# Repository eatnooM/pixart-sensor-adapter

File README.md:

# pixart-sensor-adapter

License: CC BY-SA 4.0

Allows interfacing with a Wiimote camera over I2C for GUN4IR.

Variants are present to allow use of the module either socketed as you'd find it on the Wiimote, or unsocketed for more compact installs.

I've only clocked a few hours actually _using_ these, so run this off at your own risk.

## Inline board

The inline board should be ordered in 0.8mm thickness, otherwise you won't be able to solder to the pads on the camera!
If ordering from OSHPark, I'd recommend the panelised version as they tend to put panel tabs on the edge connectors which can make for annoying cleanup before the boards are usable.

It's a pain to solder the camera module directly to the board, so I'd strongly recommend using the jig from RetroMidget's shell (see below) to aid with this, or running off [the standalone camera module jig](inline/printables/Wii-IR-camera-solder-guideGun4IR-v7.stl) graciously provided by Gzus348.

### Shell

If you're using the inline board, I would strongly recommend you check out [RetroMidget's camera enclosure](https://github.com/slikvik55/Lightgun3DParts/tree/main/WiiCamEnclosure). This 3D-printable enclosure is currently verified to fit the v1.0 board (but also fit the v1.2 board as long as you omit the rear cover) and enables you to install directly (such as in a GunCon 1) by simply tightening the nuts to hold it in place in the shell, or using prints such as JayBee's Gun4IR GunCon mounts ([GunCon 1](https://www.gun4ir.com/products/copy-of-gun4ir-diy-cam-and-rumble-holder-sets), [GunCon 2](https://www.gun4ir.com/products/gc1-gun4ir-diy-cam-and-rumble-holders)) to secure the camera and a fish-eye lens for use closer to your display.

I have a project to make a shell for the newer versions of this board that make use of the slimmer profile to fit in some tighter places (such as the barrel of a Blaze Scorpion 2, which is slightly too narrow for the DFRobot Gravity camera), but sit tight for news on this.

### IR Pass Filter

To prevent the camera from picking up visible-light sources as well as the infrared from your emitters, it is recommended to add an IR pass filter in front of the camera. This cuts down on camera erroneously detecting bright lights instead of your IR points.

If salvaging from whole Wii remotes including the shell, you'll already have the IR pass filter - this is the black-coloured plastic in the front of the shell. If you got hold of a job lot of bare boards, however, you will need to purchase some filter. I've been using the filter found in [this eBay listing](https://www.ebay.co.uk/itm/397673945348) - it's nice and thin, making it easier to cut down to size and fit in a build, and 100mm x 100mm will serve for a lot of builds if you're efficient at cutting them out. If this listing isn't available for you, there are similar listings [on Aliexpress](https://www.aliexpress.com/w/wholesale-infrared-pass-filter-940nm.html). The most important aspect of the filter is that it passes 940nm wavelength your emitters (presumably) use, and ideally blocks as much of everything else as possible.

To cut the filter, I'd recommend a rotary tool. If you have particularly sharp flush cutters, these can do the job if you're careful but I've had these split the plastic in inconvenient places so it's not my first choice. You can repeatedly score the plastic with a sharp knife to get a square of roughly the right size and then file into the desired shape, but this may take a while. You'll then need to attach this in front of the camera:

- The simplest way to attach the filter is to cut a circle of the filter to the same diameter as your shell, apply a little hot glue to the front of the shell you're using and stick it in place. If it's good enough for DFRobot, it's good enough for us. If you've dabbled in phone repair before, T7000/B7000 or similar glues will also do a great job. Just be sure to keep the glue away from the part directly in front of the camera.
- If you're using [RetroMidget's shell](https://github.com/slikvik55/Lightgun3DParts/tree/main/WiiCamEnclosure), there's a smaller circular window so you can save on a little material and only cover this area up with the filter. 

If using a wide angle or fish eye lens, there are some other convenient places to stick the filter:

- The wide angle lens adapters in the printables section all have a taper that's pretty forgiving to glue the filter into as long as you can cut it into a rough circle so there aren't big gaps for unfiltered light to pass through.
- There's a lip on the inside of the lens too - you can fit a thin filter in here.

## Ordering

Either download the gerbers from [the current release](https://github.com/eatnooM/pixart-sensor-adapter/releases/latest) or run off directly from OSHPark ([Inline](https://oshpark.com/shared_projects/reO6OkLE) / [Socketed](https://oshpark.com/shared_projects/FovxzPdv).
See below for the Bill of Materials - these can be purchased from your preferred electronic component distributor but I've provided LCSC and Mouser links for convenience.

## BOM

| Reference | Value | Link |
|-----------|-------|------|
| C1 | 0.1uF | [LCSC - YAGEO CC0603KRX7R9BB104](https://www.lcsc.com/product-detail/_YAGEO-_C14663.html) / [Mouser - KYOCERA 06035C104KAT4A](https://www.mouser.com/ProductDetail/KYOCERA-AVX/06035C104KAT4A?qs=wQ3bP3iXTzYfFzAFm7vUeQ%3D%3D) |
| C2, C3 | 1uF | [LCSC - YAGEO CC0603JRX7R7BB105](https://www.lcsc.com/product-detail/_YAGEO-_C519560.html) / [Mouser - KYOCERA 06035C105KAT2A](https://www.mouser.com/ProductDetail/KYOCERA-AVX/06035C105KAT2A?qs=%252BdQmOuGyFcGCdIIWh6fU7Q%3D%3D)|
| R1, R2 | 2.7KΩ | [LCSC - YAGEO RC0603FR-072K7L](https://www.lcsc.com/product-detail/_YAGEO-_C114612.html) / [Mouser - Panasonic ERJ-3GEYJ272V](https://www.mouser.com/ProductDetail/Panasonic/ERJ-3GEYJ272V?qs=sGAEpiMZZMvdGkrng054tw5%2FFYq5P%2FDo1QNxauZrLUw%3D) |
| R3 | 33KΩ | [LCSC - VISHAY CRCW060333K0FKEA](https://www.lcsc.com/product-detail/C844778.html) / [Mouser - Panasonic ERJ-3GEYJ333V](https://www.mouser.com/ProductDetail/Panasonic/ERJ-3GEYJ333V?qs=JjxTDIFmKPQB8Hd2hIsG7w%3D%3D) |
| U1 | Wiimote camera module – salvaged from official wiimote | Salvaged |
| U2 | AP2112-3.3V | [LCSC](https://www.lcsc.com/product-detail/_Diodes-Incorporated-_C51118.html) / [Mouser](https://www.mouser.com/productdetail/Diodes-Incorporated/AP2112K-3.3TRG1?qs=x6A8l6qLYDDPYHosCdzh%2FA%3D%3D) |
| X1 | 24-25MHz SMD3225 active crystal oscillator | [LCSC - YXC OT2EL4C4JI-111OLP-24M](https://www.lcsc.com/product-detail/Oscillators_YXC-OT2EL4C4JI-111OLP-24M_C5203548.html) / [Mouser - KYOCERA KC3225K24.0000C1GE00](https://www.mouser.com/ProductDetail/KYOCERA-AVX/KC3225K24.0000C1GE00?qs=rfsXwfL%252BOM9DBu9I0fBoew%3D%3D) |

When using with OpenFIRE, the following amendments can be made:
- As VCC is already 3.3V, U2, C2, and C3 can be omitted (and JP1 should be bridged to connect VCC straight to the camera)
- OpenFIRE supports generating the 24MHz clock signal from the RP2040 directly, meaning you can wire this to the CLK and omit X1 and C1.

## Credits

[JayBee](https://www.gun4ir.com/) - creator of Gun4IR - sharing the schematic

Gzus348 - creating the camera jig

[RetroMidget](https://github.com/slikvik55) - creator of the lovely shell for the inline boards

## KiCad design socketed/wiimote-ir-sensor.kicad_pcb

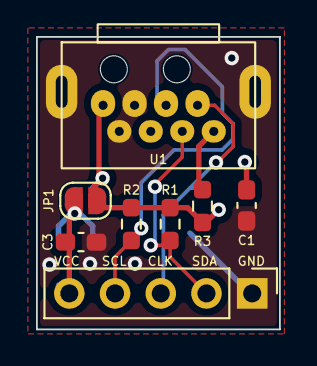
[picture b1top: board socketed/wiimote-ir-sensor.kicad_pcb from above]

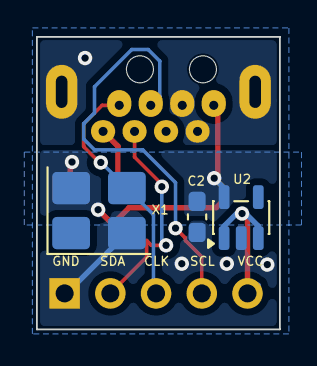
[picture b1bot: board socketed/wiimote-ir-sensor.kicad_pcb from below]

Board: 2 copper layers, 13.5 x 16.2 mm, 11 parts (3 on the bottom side), 7 nets.

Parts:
C1: 0.1uF; C_0603_1608Metric_Pad1.08x0.95mm_HandSolder
C2, C3: 1uF; C_0603_1608Metric_Pad1.08x0.95mm_HandSolder
J1: Conn_01x05_Pin; PinHeader_1x05_P2.54mm_Vertical
JP1: SolderJumper_2_Open; SolderJumper-2_P1.3mm_Open_RoundedPad1.0x1.5mm
R1, R2: 2.7K; R_0603_1608Metric_Pad0.98x0.95mm_HandSolder
R3: 33K; R_0603_1608Metric_Pad0.98x0.95mm_HandSolder
U1: wiimote-pixart-camera
U2: AP2112-3.3V; SOT-23-5
X1: SG3225CAN 24.0000M-TJGA3; Oscillator_SMD_SeikoEpson_SG8002CE-4Pin_3.2x2.5mm_HandSolde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

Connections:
+3.3V: C1.1, C2.1, JP1.2 (B), R1.1, R2.2, R3.1, U1.1 (VCC), U2.5 (VOUT), X1.4 (VCC)
/CLK: J1.3, U1.7 (CLK), X1.3 (OUT)
/SCL: J1.4, R2.1, U1.5 (SCL)
/SDA: J1.2, R1.2, U1.6 (SDA)
GND: C1.2, C2.2, C3.2, J1.1, U1.2 (GND), U1.3 (GND), U1.MP, U2.2 (GND), X1.2 (GND)
unnamed: R3.2, U1.8 (RESET)
VCC: C3.1, J1.5, JP1.1 (A), U2.1 (VIN), U2.3 (EN)

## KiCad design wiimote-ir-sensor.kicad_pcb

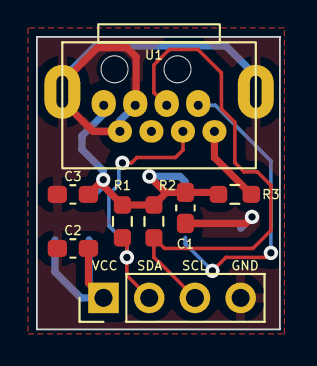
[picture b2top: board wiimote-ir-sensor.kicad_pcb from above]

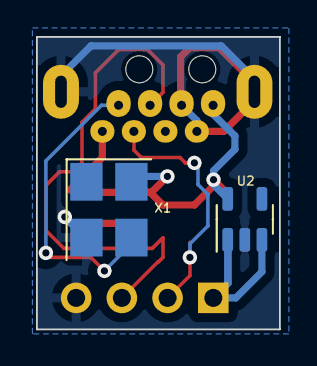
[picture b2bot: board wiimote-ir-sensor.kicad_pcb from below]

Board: 2 copper layers, 13.5 x 16.2 mm, 10 parts (2 on the bottom side), 7 nets.

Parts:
C1: 0.1uF; C_0603_1608Metric_Pad1.08x0.95mm_HandSolder
C2, C3: 1uF; C_0603_1608Metric_Pad1.08x0.95mm_HandSolder
J1: Conn_01x04_Pin; PinHeader_1x04_P2.54mm_Vertical
R1, R2: 2.7K; R_0603_1608Metric_Pad0.98x0.95mm_HandSolder
R3: 330K; R_0603_1608Metric_Pad0.98x0.95mm_HandSolder
U1: wiimote-pixart-camera
U2: AP2112-3.3V; SOT-23-5
X1: SG3225CAN 24.0000M-TJGA3; Oscillator_SMD_SeikoEpson_SG8002CE-4Pin_3.2x2.5mm_HandSolde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

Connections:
+3.3V: C1.1, C3.1, R1.1, R2.2, R3.1, U1.1 (VCC), U2.5 (VOUT), X1.4 (VCC)
+5V: C2.1, J1.1, U2.1 (VIN), U2.3 (EN)
/CLK: U1.7 (CLK), X1.3 (OUT)
/SCL: J1.3, R2.1, U1.5 (SCL)
/SDA: J1.2, R1.2, U1.6 (SDA)
GND: C1.2, C2.2, C3.2, J1.4, U1.2 (GND), U1.3 (GND), U1.MP, U2.2 (GND), X1.2 (GND)
unnamed: R3.2, U1.8 (RESET)

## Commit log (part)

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2023-08-28 First usable revision
2023-11-11 Add inline files and footprints, minor project organisation
2023-11-11 Add inline camera jig
2023-11-11 Add readme and license
2023-11-11 Update README.md
    Add OSHPark project links
2023-11-17 Add picture of assembled board
2024-03-24 Revision 2.
    - Reroute to leave more empty space on sides
    - Tweak camera footprint
    - Add castellated variant
    - Add manually panelised boards to help prevent panel tabs
    from appearing in edge connector
2024-04-26 Fix SCL/SDA silkscreen, tweak BOM
2024-04-26 Update castellated board with proper SDA/SCL labels
2024-04-26 Rev2 (#1)
    Revision 2.
    - Reroute to leave more empty space on sides
    - Tweak camera footprint
    - Add castellated variant
    - Add manually panelised boards to help prevent panel tabs
    from appearing in edge connector
2024-04-26 Update BOM
2024-04-27 Fix BOM and schematic R3 value
    (Thanks to RetroMidget for spotting this!)
2024-04-28 Update readme, OSHPark inline project link
2024-08-30 Socketed board: Tidy up
2024-08-31 More QoL tweaks to socketed board
2024-09-04 Fix regulator Mouser link
    Cheers workerbee905!
2024-09-16 WIP v1.1
2024-09-16 Instate superslim variant as new inline
2024-09-16 Rework inline board
    - Slimmer but longer board to allow for very narrow installs with tabs
    on mousebites to support existing shell size
    - Use KiKit for panelisation
    - Add jumper to skip voltage regulator for boards using 3.3v logic
    - Some support for using the panel as a crude camera soldering jig
    - Add missing footprints
2024-09-16 Rework inline board (#2)
    - Slimmer but longer board to allow for very narrow installs with tabs
    on mousebites to support existing shell size
    - Use KiKit for panelisation
    - Add jumper to skip voltage regulator for boards using 3.3v logic
    - Some support for using the panel as a crude camera soldering jig
    - Add missing footprints
2024-09-24 Update README.md
    Update to v1.1 and add Shell section
2024-09-25 Update socketed board - cleanup and add jumper to skip regulator
2024-09-29 Update README.md
    Let's try getting the license name correct!
2025-05-29 Update inline board to allow wiring clock signal directly
2026-06-12 Add 3D printable parts for inline board
2026-06-12 Cleanup
